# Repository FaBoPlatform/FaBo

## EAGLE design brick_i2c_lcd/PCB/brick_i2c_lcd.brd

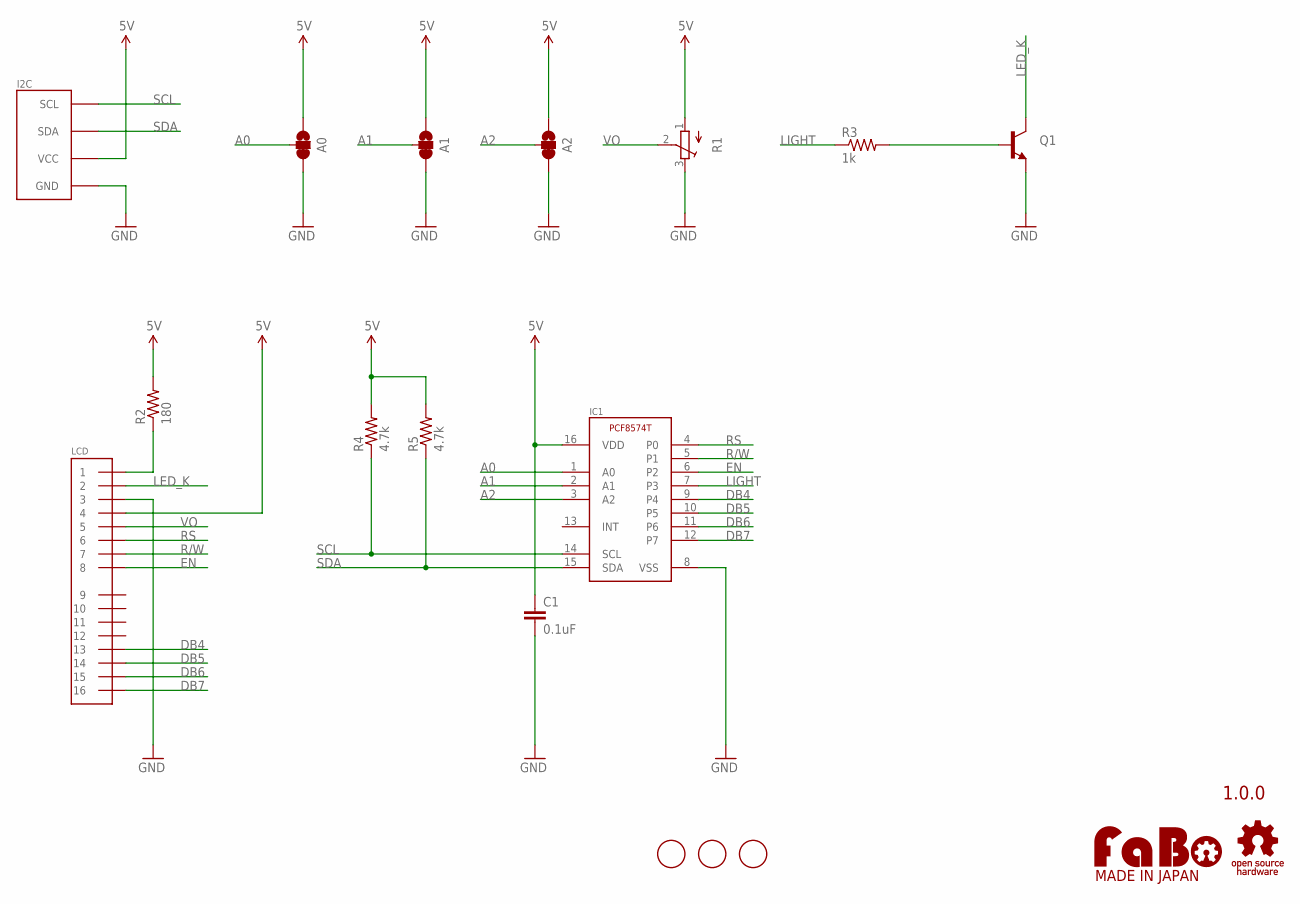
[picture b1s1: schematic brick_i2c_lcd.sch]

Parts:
A0, A1, A2: SMD-JUMPER-3-23SHORT; SMD-JUMPER-3
C1: 0.1uF; EIA0603
I2C: FABO_BRICK_I2C-CONNECTOR; FABO_BRICK_I2C_CONNECTOR
IC1: PCF8574T; SO16
LCD: PINHEAD_1X16; PIN_1X16
Q1: BC850; SOT23
R1: TRIMPOTTC33X; TC33X
R2: 180; EIA0603
R3: 1k; EIA0603
R4, R5: 4.7k; EIA0603
U$2: LOGO_OSHW-M; LOGO_OSHW_M
U$3: LOGO_FABO-M; LOGO_FABO_M
U$4, U$6, U$7: SCREW-PAD-3MM; SCREWPAD_3MM

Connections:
5V: A0.1, A1.1, A2.1, C1.1, I2C.VCC, IC1.16 (VDD), LCD.4, R1.1 (A), R2.2, R4.2, R5.2
A0: A0.2, IC1.1 (A0)
A1: A1.2, IC1.2 (A1)
A2: A2.2, IC1.3 (A2)
BASE: Q1.1 (B), R3.2
DB4: IC1.9 (P4), LCD.13
DB5: IC1.10 (P5), LCD.14
DB6: IC1.11 (P6), LCD.15
DB7: IC1.12 (P7), LCD.16
EN: IC1.6 (P2), LCD.8
GND: A0.3, A1.3, A2.3, C1.2, I2C.GND, IC1.8 (VSS), LCD.3, Q1.2 (E), R1.3 (E)
LED_A: LCD.1, R2.1
LED_K: LCD.2, Q1.3 (C)
LIGHT: IC1.7 (P3), R3.1
R/W: IC1.5 (P1), LCD.7
RS: IC1.4 (P0), LCD.6
SCL: I2C.SCL, IC1.14 (SCL), R4.1
SDA: I2C.SDA, IC1.15 (SDA), R5.1
VO: LCD.5, R1.2 (S)

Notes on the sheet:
1.0.0

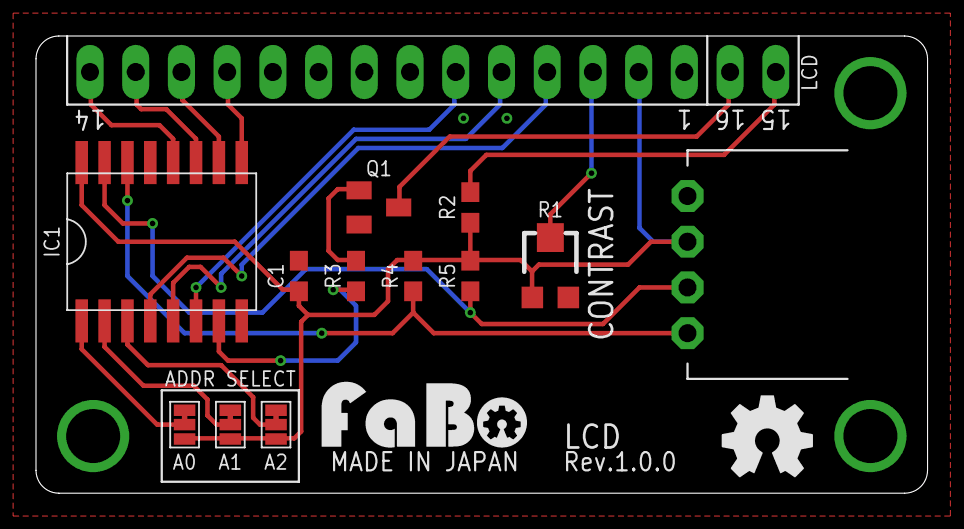
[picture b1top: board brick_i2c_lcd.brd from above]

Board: 2 copper layers, 49.5 x 25.4 mm, 18 parts (1 on the bottom side), 19 nets.

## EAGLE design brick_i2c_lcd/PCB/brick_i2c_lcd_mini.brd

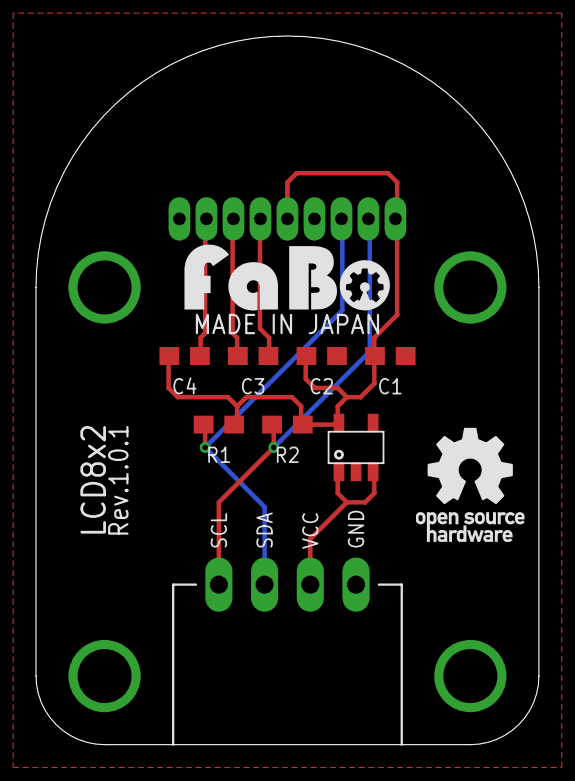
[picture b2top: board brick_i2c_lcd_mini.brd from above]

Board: 2 copper layers, 27.9 x 39.4 mm, 11 parts (0 on the bottom side), 8 nets.

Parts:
C1, C3, C4: 1uF; EIA0603
C2: 0.1uF; EIA0603
IC1: TI-LP2985
J1: FABO_BRICK_I2C
R1, R2: 4.7k; EIA0603
U1: AQM0802A
U$2: LOGO_OSHW_T_M
U$3: LOGO_FABO_M

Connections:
3V3: C1.1, C2.1, C4.1, IC1.5, R1.2, R2.2, U1.5, U1.9
5V: IC1.1, IC1.3, J1.VCC
GND: C1.2, C2.2, IC1.2, J1.GND, U1.6
unnamed: C3.2, U1.4
unnamed: C3.1, U1.3
unnamed: C4.2, U1.2
SCL: J1.SCL, R2.1, U1.8
SDA: J1.SDA, R1.1, U1.7

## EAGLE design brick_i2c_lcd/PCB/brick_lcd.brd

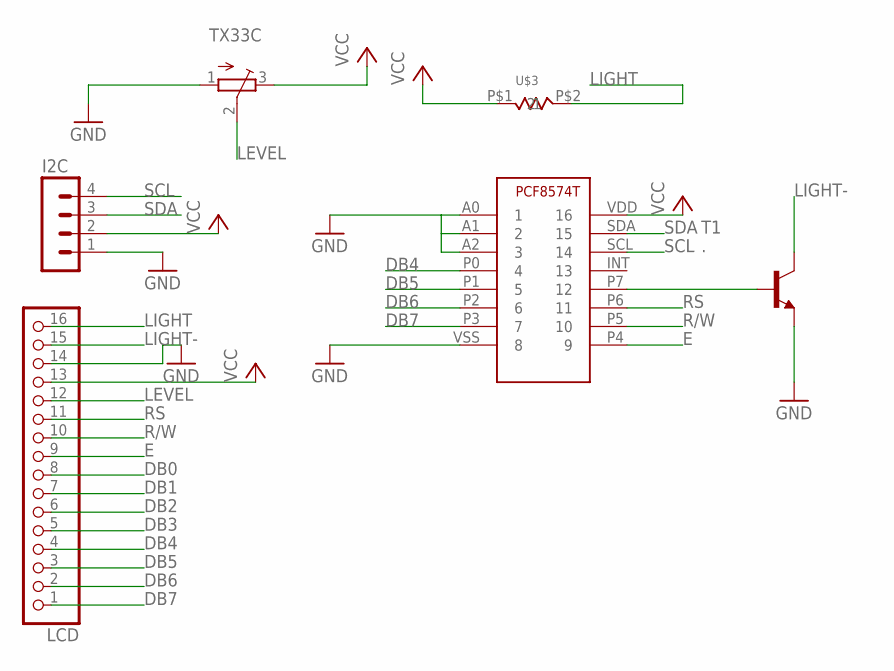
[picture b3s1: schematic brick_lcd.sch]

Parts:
I2C: MA04-1
LCD: PINHD-1X16; 1X16
T1: .; SOT23
TX33C: TRIMPOTTC33X; TC33X
U$1: IC-PCF8574T; SO16
U$3: RESISTOR_0603

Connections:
DB0: LCD.8
DB1: LCD.7
DB2: LCD.6
DB3: LCD.5
DB4: LCD.4, U$1.P0 (4)
DB5: LCD.3, U$1.P1 (5)
DB6: LCD.2, U$1.P2 (6)
DB7: LCD.1, U$1.P3 (7)
E: LCD.9, U$1.P4 (9)
GND: I2C.1, LCD.14, T1.2 (E), TX33C.1 (A), U$1.A0 (1), U$1.A1 (2), U$1.A2 (3), U$1.VSS (8)
LEVEL: LCD.12, TX33C.2 (S)
LIGHT: LCD.16, U$3.P$2 (2)
LIGHT-: LCD.15, T1.3 (C)
unnamed: T1.1 (B), U$1.P7 (12)
R/W: LCD.10, U$1.P5 (10)
RS: LCD.11, U$1.P6 (11)
SCL: I2C.4, U$1.SCL (14)
SDA: I2C.3, U$1.SDA (15)
VCC: I2C.2, LCD.13, TX33C.3 (E), U$1.VDD (16), U$3.P$1 (1)

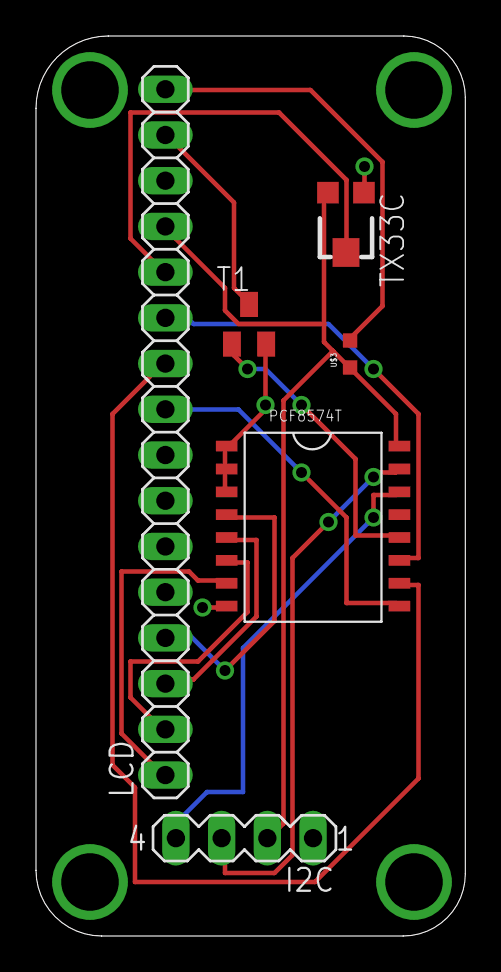
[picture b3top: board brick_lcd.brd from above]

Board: 2 copper layers, 23.9 x 50.0 mm, 6 parts (0 on the bottom side), 15 nets.

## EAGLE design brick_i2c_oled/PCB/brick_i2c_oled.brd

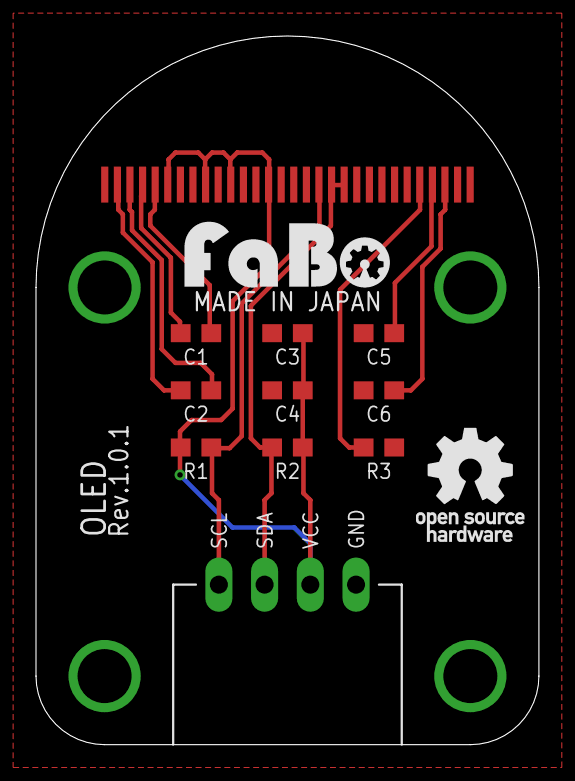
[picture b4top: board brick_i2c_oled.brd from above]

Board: 2 copper layers, 27.9 x 39.4 mm, 13 parts (0 on the bottom side), 11 nets.

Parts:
C1, C2, C3, C4: 1uF; EIA0603
C5, C6: 10uF; EIA0603
J1: FABO_BRICK_I2C
R1, R2: 4.7k; EIA0603
R3: 390k; EIA0603
U1: ER-OLED0.96-1
U$2: LOGO_OSHW_T_M
U$3: LOGO_FABO_M

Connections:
3V3: C3.1, C4.1, J1.VCC, R1.2, R2.2, U1.6, U1.9, U1.11, U1.14
GND: C3.2, C4.2, C5.2, C6.2, J1.GND, R3.1, U1.8, U1.10, U1.12, U1.13, U1.15, U1.16, U1.17, U1.21, U1.22, U1.23, U1.24, U1.25, U1.29
unnamed: C2.1, U1.2
unnamed: C2.2, U1.3
unnamed: C1.1, U1.4
unnamed: C1.2, U1.5
unnamed: C6.1, U1.28
unnamed: C5.1, U1.27
unnamed: R3.2, U1.26
SCL: J1.SCL, R1.1, U1.18
SDA: J1.SDA, R2.1, U1.19, U1.20

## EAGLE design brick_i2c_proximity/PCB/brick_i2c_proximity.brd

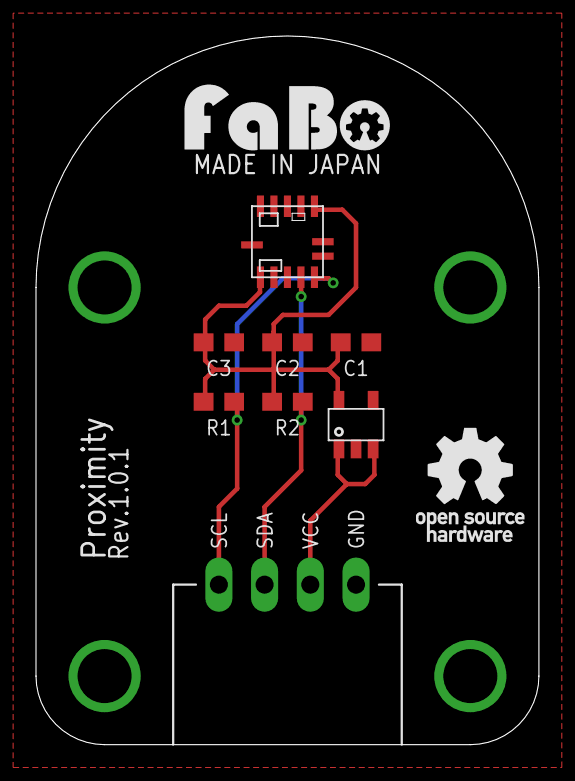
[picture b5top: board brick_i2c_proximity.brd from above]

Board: 2 copper layers, 27.9 x 39.4 mm, 10 parts (0 on the bottom side), 5 nets.

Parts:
C1: 1uF; EIA0603
C2, C3: 10uF; EIA0603
IC1: VCNL4010-GS08
IC2: TI-LP2985
J1: FABO_BRICK_I2C
R1, R2: 4.7k; EIA0603
U$2: LOGO_OSHW_T_M
U$3: LOGO_FABO_M

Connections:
3V3: C1.1, C2.1, C3.1, IC1.1, IC1.7, IC2.5, R1.2, R2.2
5V: IC2.1, IC2.3, J1.VCC
GND: C1.2, C2.2, C3.2, IC1.12, IC1.13, IC2.2, J1.GND
SCL: IC1.5, J1.SCL, R1.1
SDA: IC1.4, J1.SDA, R2.1

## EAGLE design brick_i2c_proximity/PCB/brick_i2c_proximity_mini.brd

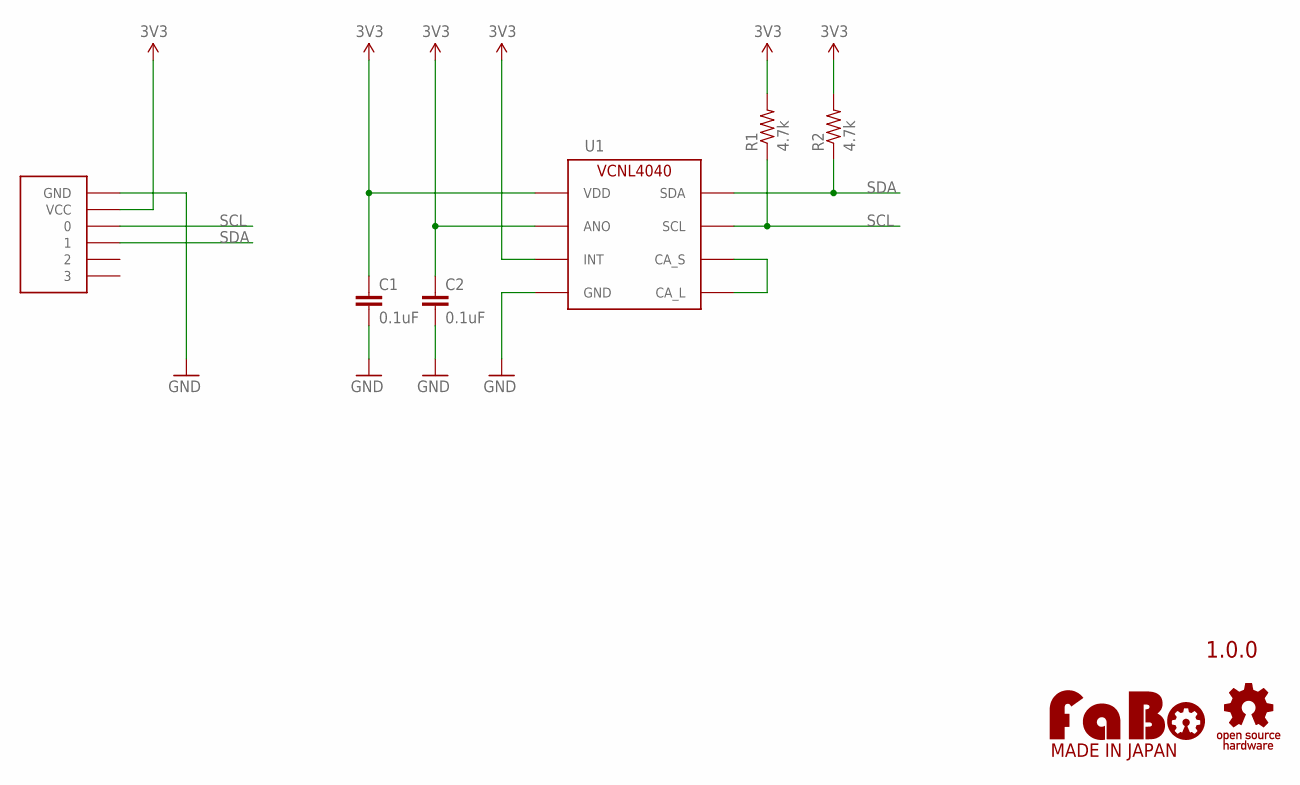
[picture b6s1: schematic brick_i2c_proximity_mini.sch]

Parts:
C1, C2: 0.1uF; EIA0603
R1, R2: 4.7k; EIA0603
U1: VCNL4040M3OE
U$2: FABO-NANO
U$3: LOGO_OSHW-S_BOTTOM; LOGO_OSHW_S_BOTTOM
U$4: LOGO_FABO-S_BOTTOM; LOGO_FABO_S_BOTTOM

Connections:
3V3: C1.1, C2.1, R1.2, R2.2, U1.3 (VDD), U1.4 (ANO), U1.6 (INT), U$2.VCC
GND: C1.2, C2.2, U1.1 (GND), U$2.GND
unnamed: U1.2 (CA_S), U1.5 (CA_L)
SCL: R1.1, U1.8 (SCL), U$2.0
SDA: R2.1, U1.7 (SDA), U$2.1

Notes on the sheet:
1.0.0

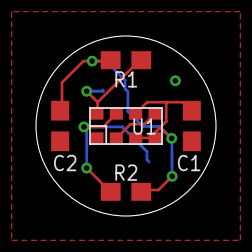
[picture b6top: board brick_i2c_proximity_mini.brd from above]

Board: 2 copper layers, 10.0 x 10.0 mm, 8 parts (0 on the bottom side), 5 nets.

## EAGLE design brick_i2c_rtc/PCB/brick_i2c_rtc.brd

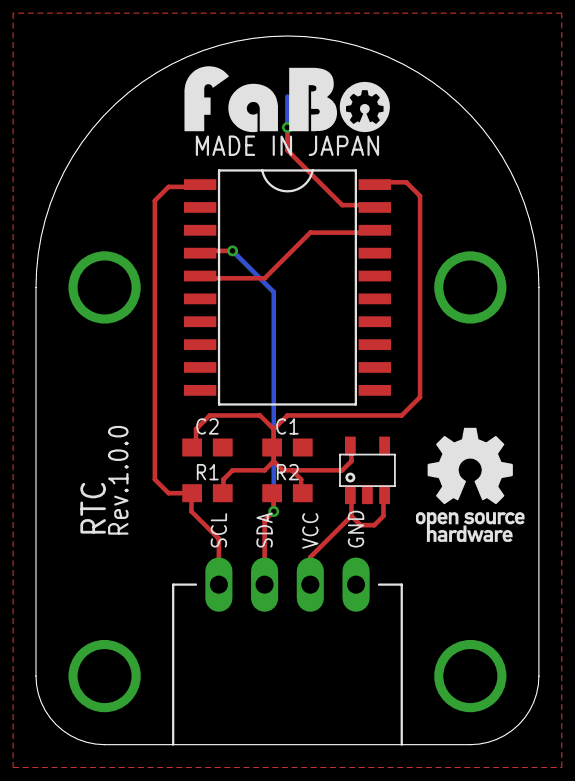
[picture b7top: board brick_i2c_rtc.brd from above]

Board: 2 copper layers, 27.9 x 39.4 mm, 10 parts (1 on the bottom side), 7 nets.

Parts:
C1: 1uF; EIA0603
C2: 0.1uF; EIA0603
IC1: SO20
IC2: TI-LP2985
J1: FABO_BRICK_I2C
R1, R2: 4.7k; EIA0603
U$2: LOGO_OSHW_T_M
U$3: LOGO_FABO_M
U$4: TAKACHI-SMTU2450

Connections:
3V3: C1.1, C2.1, IC1.20, IC2.5, R1.2, R2.2
5V: IC2.1, IC2.3, J1.VCC
GND: C1.2, C2.2, IC1.8, IC2.2, J1.GND, U$4.2
unnamed: IC1.19, U$4.1
unnamed: IC1.5, IC1.18
SCL: IC1.1, J1.SCL, R1.1
SDA: IC1.4, J1.SDA, R2.1

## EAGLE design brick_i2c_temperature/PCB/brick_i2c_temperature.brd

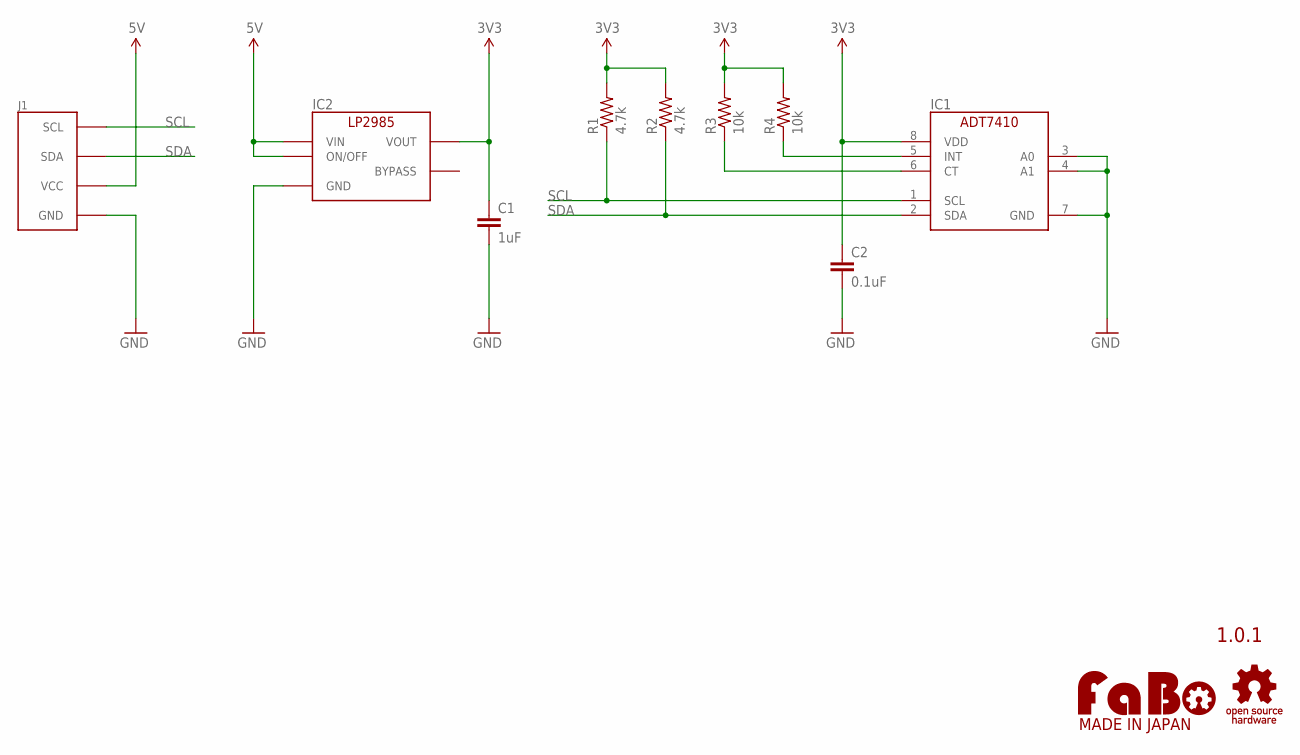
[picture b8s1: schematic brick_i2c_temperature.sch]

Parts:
C1: 1uF; EIA0603
C2: 0.1uF; EIA0603
IC1: ANALOGDEVICES-ADT7410; ADT7410
IC2: TI-LP2985-33DBVR; TI-LP2985
J1: FABO_BRICK_I2C
R1, R2: 4.7k; EIA0603
R3, R4: 10k; EIA0603
U$1: LOGO_OSHW-T_M; LOGO_OSHW_T_M
U$3: LOGO_FABO-M; LOGO_FABO_M

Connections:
3V3: C1.1, C2.1, IC1.8 (VDD), IC2.5 (VOUT), R1.2, R2.2, R3.2, R4.2
5V: IC2.1 (VIN), IC2.3 (ON/OFF), J1.VCC
GND: C1.2, C2.2, IC1.3 (A0), IC1.4 (A1), IC1.7 (GND), IC2.2 (GND), J1.GND
unnamed: IC1.6 (CT), R3.1
unnamed: IC1.5 (INT), R4.1
SCL: IC1.1 (SCL), J1.SCL, R1.1
SDA: IC1.2 (SDA), J1.SDA, R2.1

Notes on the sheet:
1.0.1

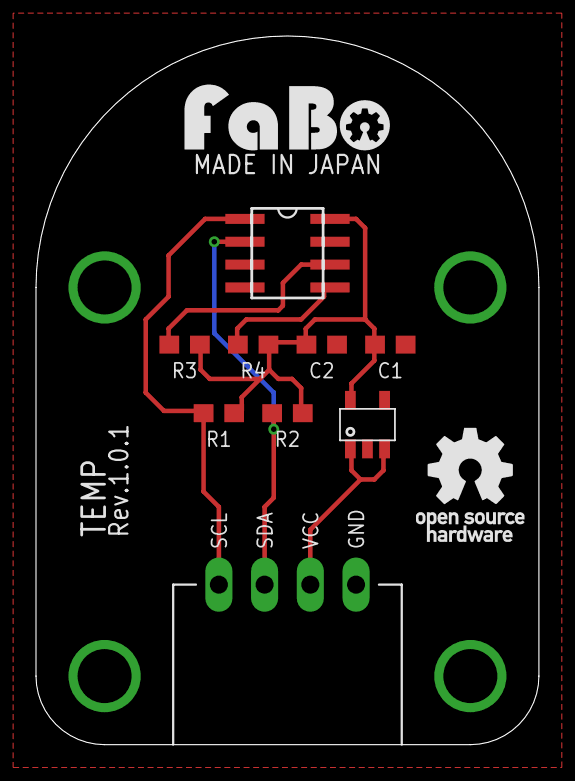
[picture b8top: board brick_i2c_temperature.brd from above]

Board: 2 copper layers, 27.9 x 39.4 mm, 11 parts (0 on the bottom side), 7 nets.

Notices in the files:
parts and their libraries:
FaBo-etc: Released under the Creative Commons Attribution-ShareAlike 4.0 License
https://creativecommons.org/licenses/by-sa/4.0
FaBo-etc: Released under the Creative Commons
